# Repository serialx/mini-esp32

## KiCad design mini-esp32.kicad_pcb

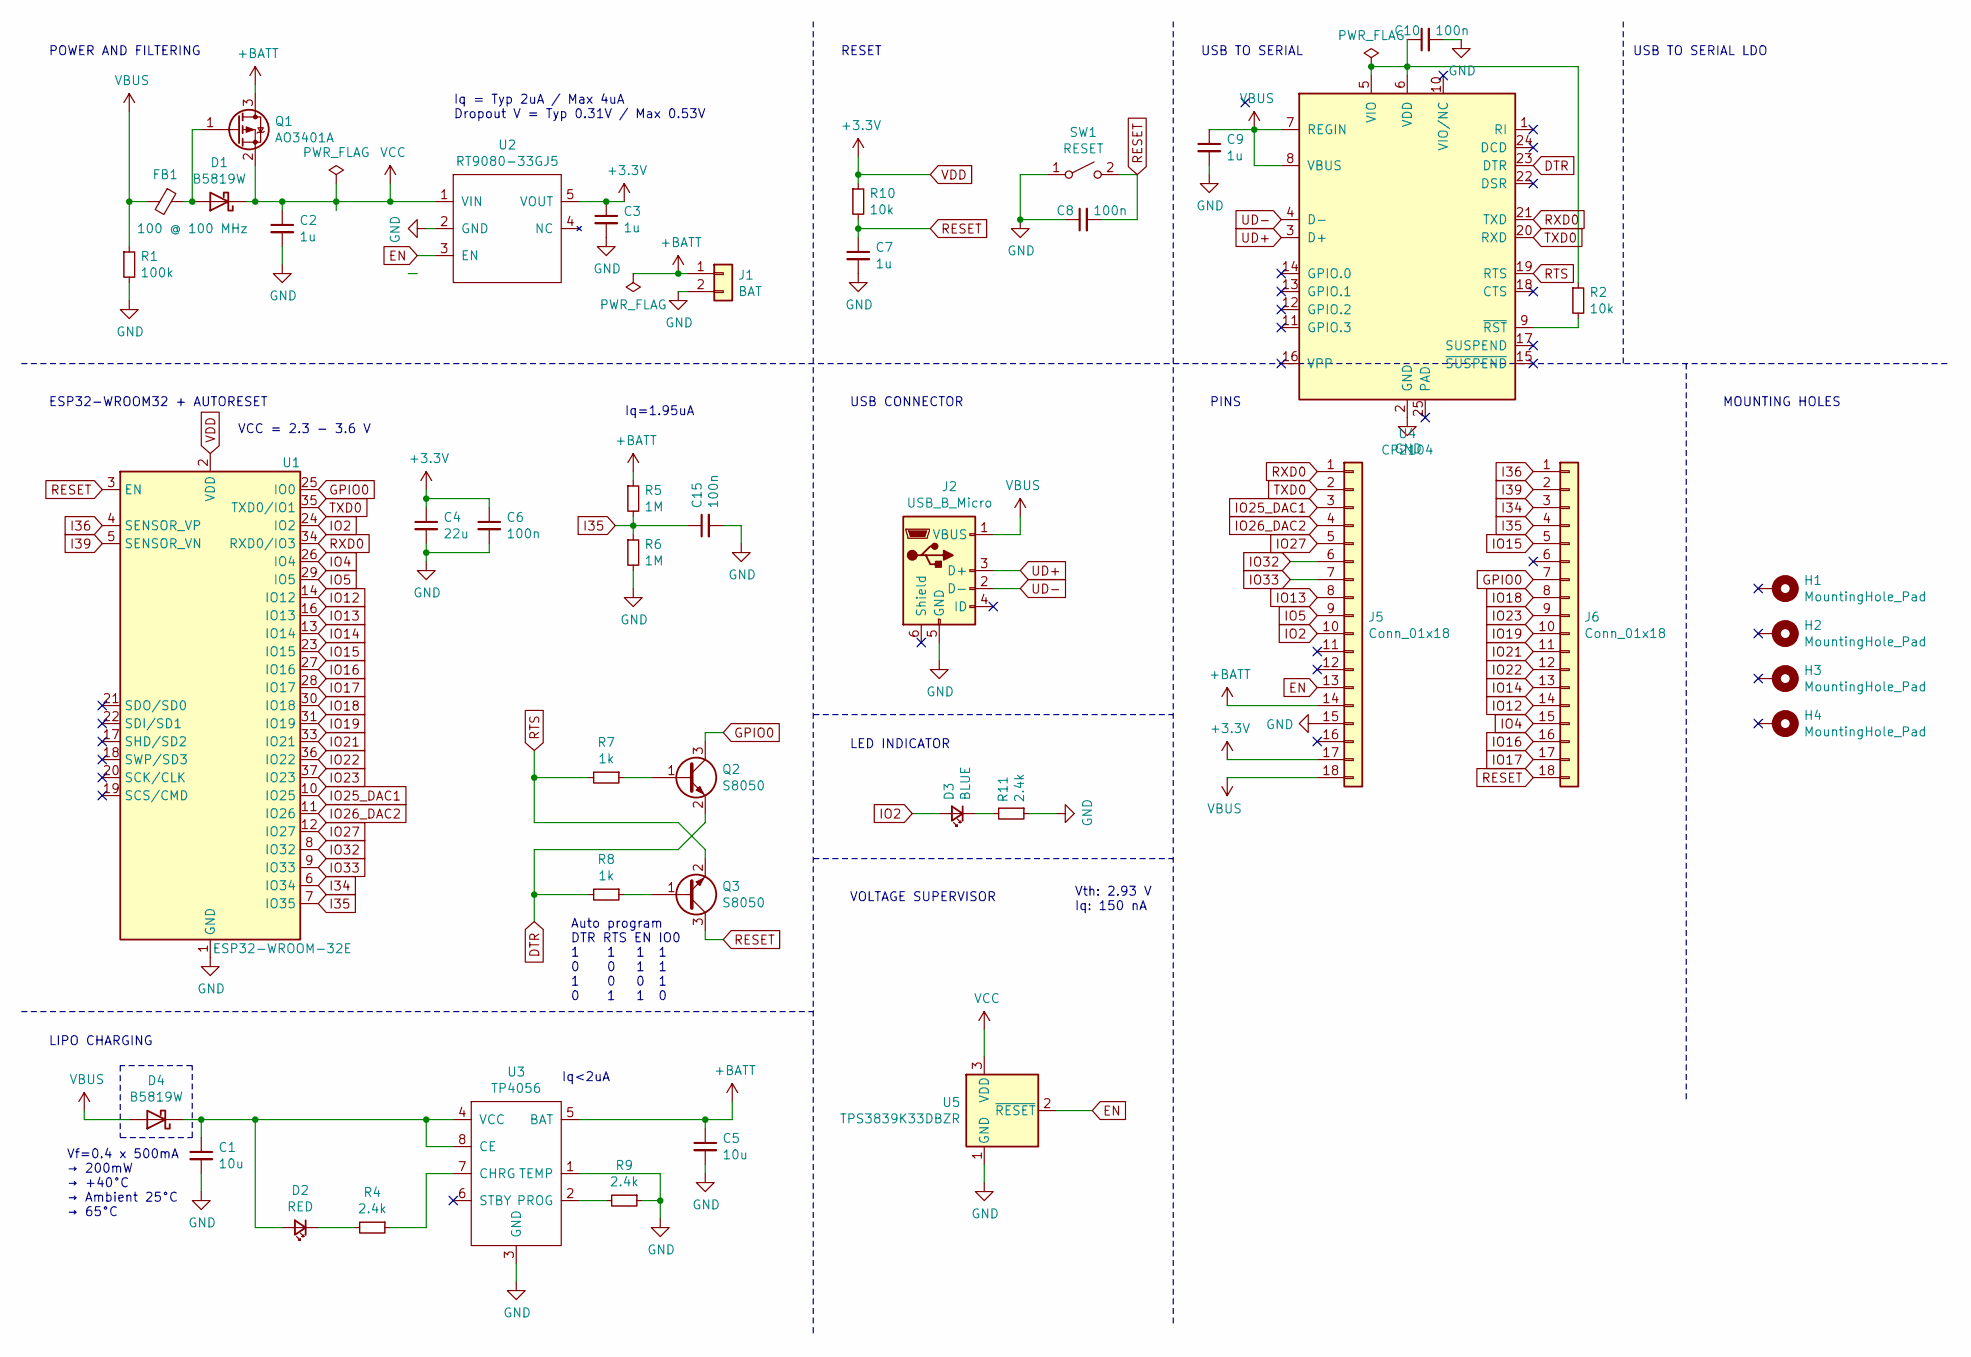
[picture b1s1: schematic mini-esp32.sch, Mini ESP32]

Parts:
C1, C5: 10u; C_0603_1608Metric; LCSC Part # C19702
C2, C3, C7, C9: 1u; C_0402_1005Metric; LCSC Part # C52923
C4: 22u; C_0603_1608Metric; LCSC Part # C59461
C6, C8, C10, C15: 100n; C_0402_1005Metric; LCSC Part # C1525
D1, D4: B5819W; D_SOD-123; LCSC Part # C8598
D2: RED; LED_0603_1608Metric; LCSC Part # C2286
D3: BLUE; LED_0603_1608Metric; LCSC Part # C72041
FB1: 100 @ 100 MHz; L_0805_2012Metric; LCSC Part # C1015
H1, H2, H3, H4: MountingHole_Pad; MountingHole_3mm
J1: BAT; JST_PH_B2B-PH-SM4-TB_1x02-1MP_P2.00mm_Vertical; LCSC Part # C146053
J2: USB_B_Micro; USB_Micro-B_Jing-C10418-A01SB141B1-067; LCSC Part # C10418
J5, J6: Conn_01x18; PinSocket_1x18_P2.54mm_Vertical
Q1: AO3401A; SOT-23; LCSC Part # C15127
Q2, Q3: S8050; SOT-23; LCSC Part # C2146
R1: 100k; R_0402_1005Metric; LCSC Part # C25741
R2, R10: 10k; R_0402_1005Metric; LCSC Part # C25744
R4, R9, R11: 2.4k; R_0603_1608Metric; LCSC Part # C22940
R5, R6: 1M; R_0402_1005Metric; LCSC Part # C26083
R7, R8: 1k; R_0402_1005Metric; LCSC Part # C11702
SW1: RESET; SW_SPST_TL3342; LCSC Part # C318887
U1: ESP32-WROOM-32E; ESP32-WROOM-32; LCSC Part # C701341
U2: RT9080-33GJ5; TSOT-23-5; LCSC Part # C841192
U3: TP4056; SOP-8_3.9x4.9mm_P1.27mm; LCSC Part # C16581
U4: CP2104; QFN-24-1EP_4x4mm_P0.5mm_EP2.6x2.6mm; LCSC Part # C47742
U5: TPS3839K33DBZR; SOT-23; LCSC Part # C96333

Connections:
+BATT: C5.1, J1.1, J5.14, Q1.3 (D), R5.1, U3.5 (BAT)
DTR: Q2.2 (E), R8.2, U4.23 (DTR)
EN: J5.13, U2.3 (EN), U5.2 (~RESET)
GND: C1.2, C2.2, C3.2, C4.2, C5.2, C6.2, C7.2, C8.1, C9.2, C10.2, C15.2, J1.2, J2.5 (GND), J5.15, R1.2, R6.2, R9.1, R11.1, SW1.1 (A), U1.1 (GND), U1.15 (GND), U1.38 (GND), U1.39 (GND), U2.2 (GND), U3.1 (TEMP), U3.3 (GND), U4.2 (GND), U5.1 (GND)
GPIO0: J6.7, Q2.3 (C), U1.25 (IO0)
I34: J6.3, U1.6 (IO34)
I35: C15.1, J6.4, R5.2, R6.1, U1.7 (IO35)
I36: J6.1, U1.4 (SENSOR_VP)
I39: J6.2, U1.5 (SENSOR_VN)
IO2: D3.2 (A), J5.10, U1.24 (IO2)
IO4: J6.15, U1.26 (IO4)
IO5: J5.9, U1.29 (IO5)
IO12: J6.14, U1.14 (IO12)
IO13: J5.8, U1.16 (IO13)
IO14: J6.13, U1.13 (IO14)
IO15: J6.5, U1.23 (IO15)
IO16: J6.16, U1.27 (IO16)
IO17: J6.17, U1.28 (IO17)
IO18: J6.8, U1.30 (IO18)
IO19: J6.10, U1.31 (IO19)
IO21: J6.11, U1.33 (IO21)
IO22: J6.12, U1.36 (IO22)
IO23: J6.9, U1.37 (IO23)
IO25_DAC1: J5.3, U1.10 (IO25)
IO26_DAC2: J5.4, U1.11 (IO26)
IO27: J5.5, U1.12 (IO27)
IO32: J5.6, U1.8 (IO32)
IO33: J5.7, U1.9 (IO33)
unnamed: C1.1, D2.2 (A), D4.1 (K), U3.4 (VCC), U3.8 (CE)
unnamed: C10.1, R2.1, U4.5 (VIO), U4.6 (VDD)
unnamed: D1.2 (A), FB1.1, Q1.1 (G)
unnamed: D2.1 (K), R4.2
unnamed: D3.1 (K), R11.2
unnamed: Q2.1 (B), R7.1
unnamed: Q3.1 (B), R8.1
unnamed: R2.2, U4.9 (~RST)
unnamed: R4.1, U3.7 (CHRG)
unnamed: R9.2, U3.2 (PROG)
RESET: C7.1, C8.2, J6.18, Q3.3 (C), R10.2, SW1.2 (B), U1.3 (EN)
RTS: Q3.2 (E), R7.2, U4.19 (RTS)
RXD0: J5.1, U1.34 (RXD0/IO3), U4.21 (TXD)
TXD0: J5.2, U1.35 (TXD0/IO1), U4.20 (RXD)
UD+: J2.3 (D+), U4.3 (D+)
UD-: J2.2 (D-), U4.4 (D-)
VBUS: C9.1, D4.2 (A), FB1.2, J2.1 (VBUS), J5.18, R1.1, U4.7 (REGIN), U4.8 (VBUS)
VCC: C2.1, D1.1 (K), Q1.2 (S), U2.1 (VIN), U5.3 (VDD)
VDD: C3.1, C4.1, C6.1, J5.17, R10.1, U1.2 (VDD), U2.5 (VOUT)

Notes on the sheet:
POWER AND FILTERING
RESET
USB TO SERIAL
ESP32-WROOM32 + AUTORESET
LIPO CHARGING
LED INDICATOR
MOUNTING HOLES
PINS
USB CONNECTOR
VOLTAGE SUPERVISOR
Vf=0.4 x 500mA → 200mW → +40°C → Ambient 25°C → 65°C
Vth: 2.93 V Iq: 150 nA
Iq<2uA
Iq=1.95uA
USB TO SERIAL LDO
Iq = Typ 2uA / Max 4uA Dropout V = Typ 0.31V / Max 0.53V
VCC = 2.3 - 3.6 V
Auto program DTR RTS EN IO0 1 1 1 1 0 0 1 1 1 0 0 1 0 1 1 0

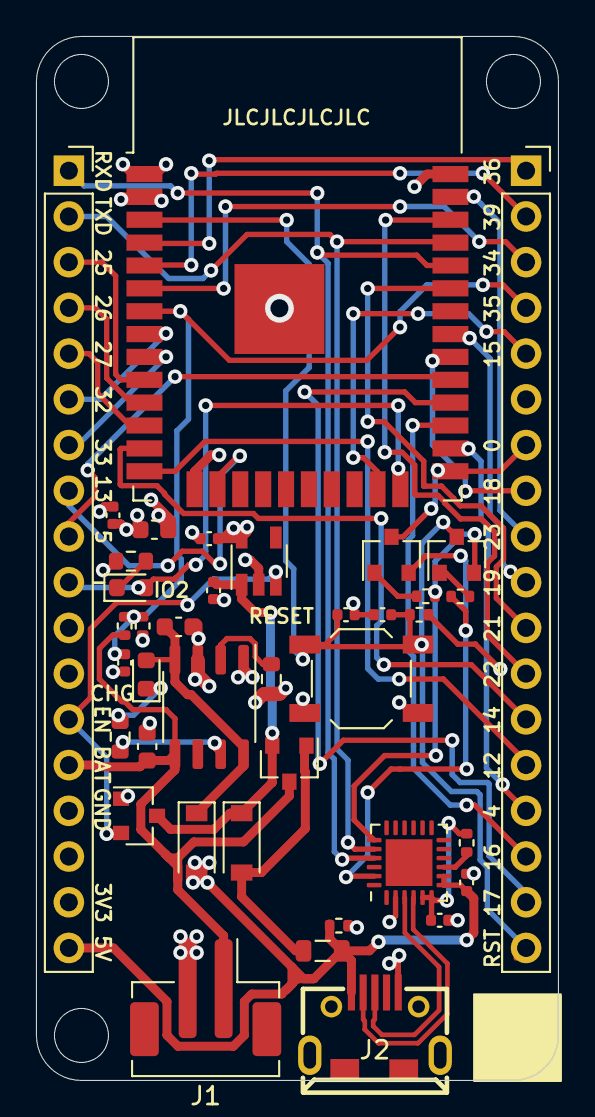
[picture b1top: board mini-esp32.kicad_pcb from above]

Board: 4 copper layers, 29.0 x 58.0 mm, 43 parts (0 on the bottom side), 47 nets.

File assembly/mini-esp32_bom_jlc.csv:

"Comment","Designator","Footprint","LCSC Part #"
"10u","C1,C5","C_0603_1608Metric","C19702"
"1u","C2,C3,C7,C9","C_0402_1005Metric","C52923"
"22u","C4","C_0603_1608Metric","C59461"
"100n","C6,C8,C15,C10","C_0402_1005Metric","C1525"
"B5819W","D1,D4","D_SOD-123","C8598"
"RED","D2","LED_0603_1608Metric","C2286"
"BLUE","D3","LED_0603_1608Metric","C72041"
"100 @ 100 MHz","FB1","L_0805_2012Metric","C1015"
"BAT","J1","JST_PH_B2B-PH-SM4-TB_1x02-1MP_P2.00mm_Vertical","C146053"
"USB_B_Micro","J2","USB_Micro-B_Jing-C10418-A01SB141B1-067","C10418"
"AO3401A","Q1","SOT-23","C15127"
"S8050","Q2,Q3","SOT-23","C2146"
"100k","R1","R_0402_1005Metric","C25741"
"2.4k","R4,R9,R11","R_0603_1608Metric","C22940"
"1M","R5,R6","R_0402_1005Metric","C26083"
"1k","R7,R8","R_0402_1005Metric","C11702"
"10k","R10,R2","R_0402_1005Metric","C25744"
"RESET","SW1","SW_SPST_TL3342","C318887"
"ESP32-WROOM-32E","U1","ESP32-WROOM-32","C701341"
"RT9080-33GJ5","U2","TSOT-23-5","C841192"
"TP4056","U3","SOP-8_3.9x4.9mm_P1.27mm","C16581"
"CP2104","U4","QFN-24-1EP_4x4mm_P0.5mm_EP2.6x2.6mm","C47742"
"TPS3839K33DBZR","U5","SOT-23","C96333"

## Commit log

2020-11-01 Initial commit. v2.0
2020-11-01 Rename files
2020-11-01 Fix power/gnd planes in the antenna zone.
2020-11-02 Fix USB Micro B footprint to official one
2020-11-02 Pad courtyard adjustment. ESP32 GND pad larger hole. Etc. V2.0.1
2020-11-04 Improved routing. Internal layers are not used anymore for routing.
2020-11-04 Gerber output. V2.0.2
2020-11-04 Add FS312F-G battery protection IC
2020-11-05 Polishing. V2.1.0
2020-11-13 Fix three critical bugs
    1. Fix RXD TXD wiring
    2. Fix LDO EN pin resistor
    3. Fix programming not working (DTR RTS programming transistor resistor values)
2020-11-14 Fix more critical bugs
    Fix NPN transistor pin mapping.
    Re-add LDO EN pin pull up resistor.
    Fix battery protection IC wiring and components to recommendation.
2020-11-15 Add PDF
2020-11-17 Fix CH340G. Backside pin numbering.
    - Crystal cap to 22pF from 33pf like the reference implementation.
    - Fix CH340G VCC to use an extra LDO instead of using RT9080 with a N MOSFET. N MOSFET to the GND seems to interfere with the CH340G's USB signalling.
    - Backside silkscreen pin numbering
2020-11-17 Change 0.1R TP4056 resistor to a diode
    Helps with the heat issues of TP4056.
2020-11-17 Extra GND heat dissipation for TP4056
2020-11-17 Add comments in the schematic
2020-11-17 Lower leakage current on battery voltage divider. Add caps.
2020-11-17 Fix EN pin cap to increase startup delay. Cheaper main bulk cap.
    Improve thermals for D4 diode. (For charging)
2020-11-17 Inspection. Tuning. Gerber & assembly files.
2020-11-21 Add notes for auto programming circuit
2020-11-25 Use TPS3839 instead of battery OC/OD. Lower power usage.
2020-11-25 Gerber and assembly for 4.0
2020-11-25 Missing commit
2020-12-13 Change USB-to-Serial to CP2104
2021-03-18 Fix broken symbol link
